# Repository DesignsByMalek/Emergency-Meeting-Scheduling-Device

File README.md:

# Integrated Documentation: Remote Emergency Meeting Scheduling Device

This comprehensive documentation merges two interconnected projects, combining IoT-enabled emergency scheduling with a Flask application to manage Google services. Together, they offer a robust solution for automating critical communication tasks.

---

## Project Overview

### License

This project is licensed under the Apache License 2.0. You may obtain a copy of the License at:

[Apache License 2.0](http://www.apache.org/licenses/LICENSE-2.0)

Unless required by applicable law or agreed to in writing, software distributed under the License is distributed on an "AS IS" BASIS, WITHOUT WARRANTIES OR CONDITIONS OF ANY KIND, either express or implied. See the License for the specific language governing permissions and limitations under the License.

---

### Remote Emergency Meeting Scheduling Device
An open-source IoT solution designed to automate emergency meeting scheduling. It integrates seamlessly with Google Meet, SMS triggers, and email notifications to enhance reliability and efficiency.

### Flask Application
A lightweight web application utilizing Google services to automate calendar and spreadsheet management, with SMS processing to trigger calendar invites.

---

## Features

### IoT Device Highlights
- **SMS Trigger**: Activates the backend server via Twilio to initiate emergency meeting scheduling.
- **Battery Efficiency**: Operates for over a year on a single battery.
- **Design Optimization**: Iteratively developed for enhanced functionality and aesthetics.
- **Complete Resources**: Includes PCB designs, 3D models, schematics, and manufacturing files.

### Backend Capabilities
- **Google Workspace Integration**: Automates Google Meet scheduling and retrieves client data from Google Sheets.
- **Email Notifications**: Sends meeting details to participants promptly.
- **Scalability**: Handles multiple requests in real-time.

### Flask App Features
- **Google Calendar Management**: Creates and customizes Google Calendar events, including attendees, timings, and reminders.
- **Spreadsheet Management**: Reads, writes, and appends data dynamically to Google Sheets.
- **SMS Processing**: Logs SMS data, retrieves client details, and triggers calendar invites based on the content.

---

## Installation

### Prerequisites
- **Software**: Python 3.8+
- **Google APIs**: Enable Calendar and Sheets APIs in the Google Cloud Console.
- **API Accounts**: Twilio account for SMS handling; OAuth credentials for Google services.

### Setup Steps

#### Clone the Repository
```bash
git clone <repository_url>
cd <repository_folder>
```

#### Install Dependencies
```bash
pip install -r requirements.txt
```

#### Configure API Credentials
- Save the credentials JSON file from Google Cloud in the project directory.
- Add API keys and credentials in `config.py`:
  ```python
  CREDENTIAL_FILE = 'path_to_credentials.json'
  CALENDAR_TOKEN = 'path_to_google_calendar_token.json'
  SHEET_TOKEN = 'path_to_google_sheet_token.json'
  GOOGLE_SHEET = 'spreadsheet_id'
  ```

#### Start the Server
```bash
python app.py
```

---

## Usage

### IoT Device
1. Activate the device to send an SMS trigger to the backend.
2. The backend:
   - Retrieves client details from Google Sheets.
   - Schedules a Google Meet session.
   - Sends email notifications to participants.

### Flask App

#### Calendar Management
- Use the `set_calendar` function to create events:
  ```python
  from modules.calendar_v1 import set_calendar

  invitees = ["example1@gmail.com", "example2@gmail.com"]
  set_calendar(invitees)
  ```

#### Google Sheets Management
- Perform operations with the `GoogleSheets` class:
  ```python
  from modules.sheets_v1 import GoogleSheets

  gs = GoogleSheets()
  # Read data
  data = gs.read_data("Sheet1", "A1:C10")
  print(data)
  # Write data
  values = [["Name", "Age"], ["Alice", 25], ["Bob", 30]]
  gs.write_data("Sheet1", "A1", values)
  # Append data
  new_rows = [["Charlie", 35]]
  gs.append_data("Sheet1", new_rows)
  ```

#### SMS Processing
- Endpoint for SMS:
  ```bash
  /emergency-button/inbound-emergency
  ```
- Example payload:
  ```json
  {
    "From": "+1234567890",
    "To": "+0987654321",
    "Body": "button_id,event_type,battery_health"
  }
  ```
- Functionality:
  - Logs SMS details to the `SMS Logs` sheet.
  - Retrieves client emails from the `Client Info` sheet.
  - Triggers calendar invites based on the SMS content.

---

## GoogleAuthenticator Class for Google API Authentication

### Description
The `GoogleAuthenticator` class is designed to streamline authentication with Google API services. It handles token management, credential verification, and API service building, making it easier to integrate with Google services like Calendar and Sheets.

### How It Works

#### Authentication Process
- Ensures tokens are valid or refreshes them if expired.
- Launches a local server to authenticate and save credentials if no token exists.
- Saves credentials for future use.

#### Service Building
- Builds a Google API service using authenticated credentials for interaction with APIs like Calendar and Sheets.

#### Example Use
- Authenticate and initialize Calendar API service:
  ```python
  from services.authenticator import GoogleAuthenticator

  auth = GoogleAuthenticator(service_name='calendar', version='v3')
  credentials = auth.get_authenticated(token_path='path/to/token.json', scope=['https://www.googleapis.com/auth/calendar'])
  calendar_service = auth.auth_build('calendar', 'v3', credentials)
  print("Calendar API initialized.")
  ```

---

## Python Code Structure

```
project_root/
    |- app/
    |   |- modules/
    |   |   |- calendar_v1.py   # Manages Google Calendar events
    |   |   |- sheets_v1.py     # Manages Google Sheets interactions
    |   |- services/
    |       |- authenticator.py # Google API authentication utility
    |   |- routes/
    |       |- sms.py           # Handles SMS processing and calendar integration
    |   |- config.py                 # Configuration file for environment variables
    |- app.py # Entry point
```
## Python Flow Chart 

---

## Future Improvements

- Enhance error handling for API operations.
- Add support for additional notification methods and triggers.
- Integrate further Google APIs for expanded functionality.
- PCB modifications for better user experience.

## IoT Device Code Highlights

### Key Functionalities
The Arduino code is designed to efficiently manage emergency meeting triggers. Below are the main highlights:

#### 1. **Low Power Mode**
The device leverages the `LowPower` library to maximize battery life by entering sleep mode when inactive.  
Example:
```cpp
#include "LowPower.h"

void sleepNow() {
    LowPower.powerDown(SLEEP_8S, ADC_OFF, BOD_OFF);  // Sleep for 8 seconds
}
```

#### 2. **Button Press Handling**
An interrupt is used to detect button presses and wake the device from sleep mode.
```cpp
const int buttonPin = 2;
volatile bool buttonPressed = false;

void setup() {
    attachInterrupt(digitalPinToInterrupt(buttonPin), wakeUp, FALLING);  // Attach interrupt
}

void wakeUp() {
    buttonPressed = true;  // Set flag on button press
}
```

#### 3. **SIM800L Communication**
The device uses `SoftwareSerial` to communicate with the SIM800L module for sending SMS triggers.
```cpp
#include <SoftwareSerial.h>

SoftwareSerial mySerial(3, 4);  // SIM800L Tx & Rx connected to pins 3 & 4

void sendSMS() {
    mySerial.begin(9600);
    mySerial.print("AT+CMGF=1
");  // Set SMS mode
    mySerial.print("AT+CMGS="+1234567890"
");  // Specify recipient
    mySerial.print("Emergency meeting triggered.
");  // Message content
    mySerial.write(26);  // End message with CTRL+Z
}
```
---

## Arduino Flow Chart

---

### Full Code
The complete code is available in the GitHub repository.

---

## Assembly Animation

---

## Done By

This project was created and maintained by:

- [GitDevKarim](https://github.com/GitDevKarim)
- [DesignsByMalek](https://github.com/DesignsByMalek)

Feel free to reach out to us for any questions or contributions!

<div style="display: flex; justify-content: center; align-items: center;">
  <div style="text-align: center; margin-right: 20px;">
    <h3>GitDevKarim</h3>
    <span style="display: inline-block; margin-right: 10px;">
      
    </span>
    <span style="display: inline-block;">
      
    </span>
  </div>

  <div style="height: 50px; width: 1px; background-color: #000;"></div>

  <div style="text-align: center; margin-left: 20px;">
    <h3>DesignsByMalek</h3>
    <span style="display: inline-block; margin-right: 10px;">
      
    </span>
    <span style="display: inline-block;">
      
    </span>
  </div>
</div>

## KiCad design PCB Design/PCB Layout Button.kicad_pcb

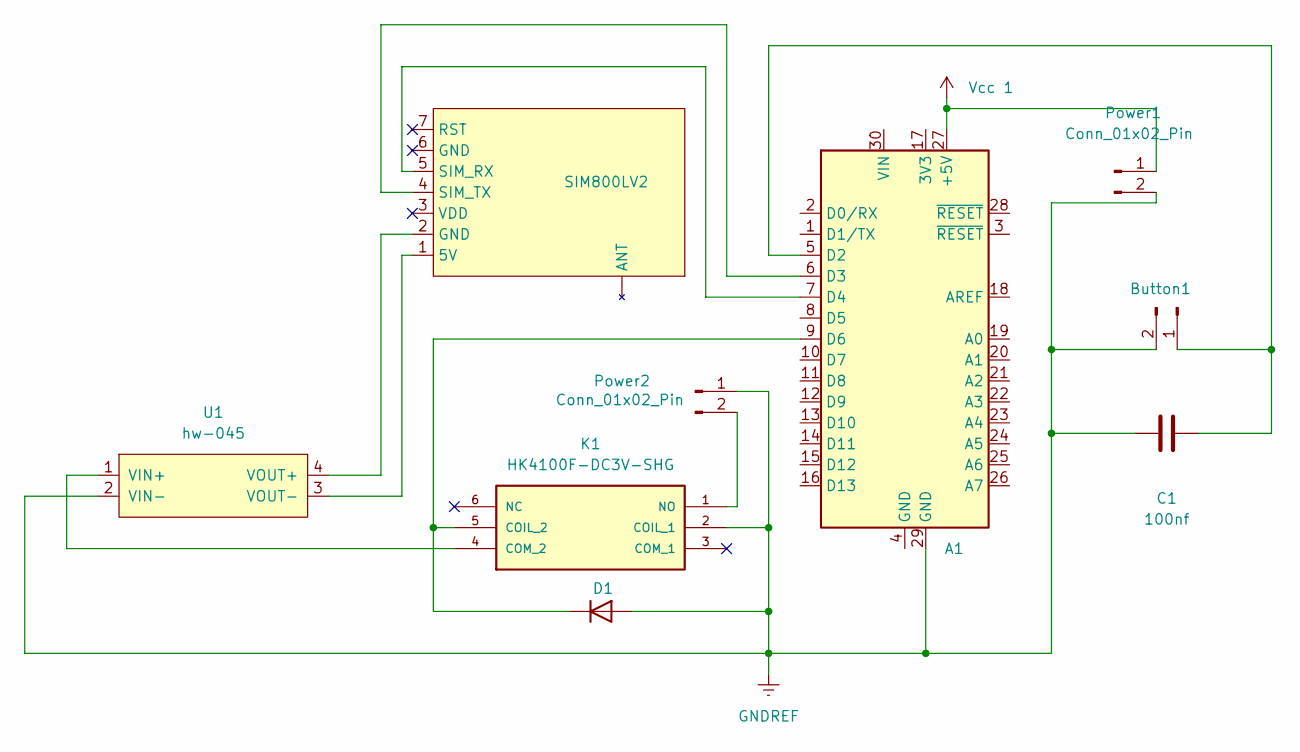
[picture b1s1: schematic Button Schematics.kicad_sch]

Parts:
A1: Arduino_Nano_v3.x; Arduino_Nano
Button1: Conn_01x02_Pin; JST_EH_B2B-EH-A_1x02_P2.50mm_Vertical
C1: 100nf; C_Disc_D5.1mm_W3.2mm_P5.00mm
D1: D; D_DO-35_SOD27_P7.62mm_Horizontal
K1: HK4100F-DC3V-SHG; HK4100FDC5VSHG; MANUFACTURER_PART_NUMBER HK4100F-DC5V-SHG
Power1, Power2: Conn_01x02_Pin; JST_EH_B2B-EH-A_1x02_P2.50mm_Vertical
SIM800LV2: SIM800
U1: hw-045; MT3608_module

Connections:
GNDREF: A1.29 (GND), Button1.2, C1.1, D1.2 (A), K1.2 (COIL_1), Power1.2, Power2.1, U1.2 (VIN-)
unnamed: A1.5 (D2), Button1.1, C1.2
unnamed: A1.6 (D3), SIM800LV2.4 (SIM_TX)
unnamed: A1.7 (D4), SIM800LV2.5 (SIM_RX)
unnamed: A1.9 (D6), D1.1 (K), K1.5 (COIL_2)
unnamed: K1.4 (COM_2), U1.1 (VIN+)
unnamed: K1.1 (NO), Power2.2
unnamed: SIM800LV2.1 (5V), U1.3 (VOUT-)
unnamed: SIM800LV2.2 (GND), U1.4 (VOUT+)
Vcc 1: A1.27 (+5V), Power1.1

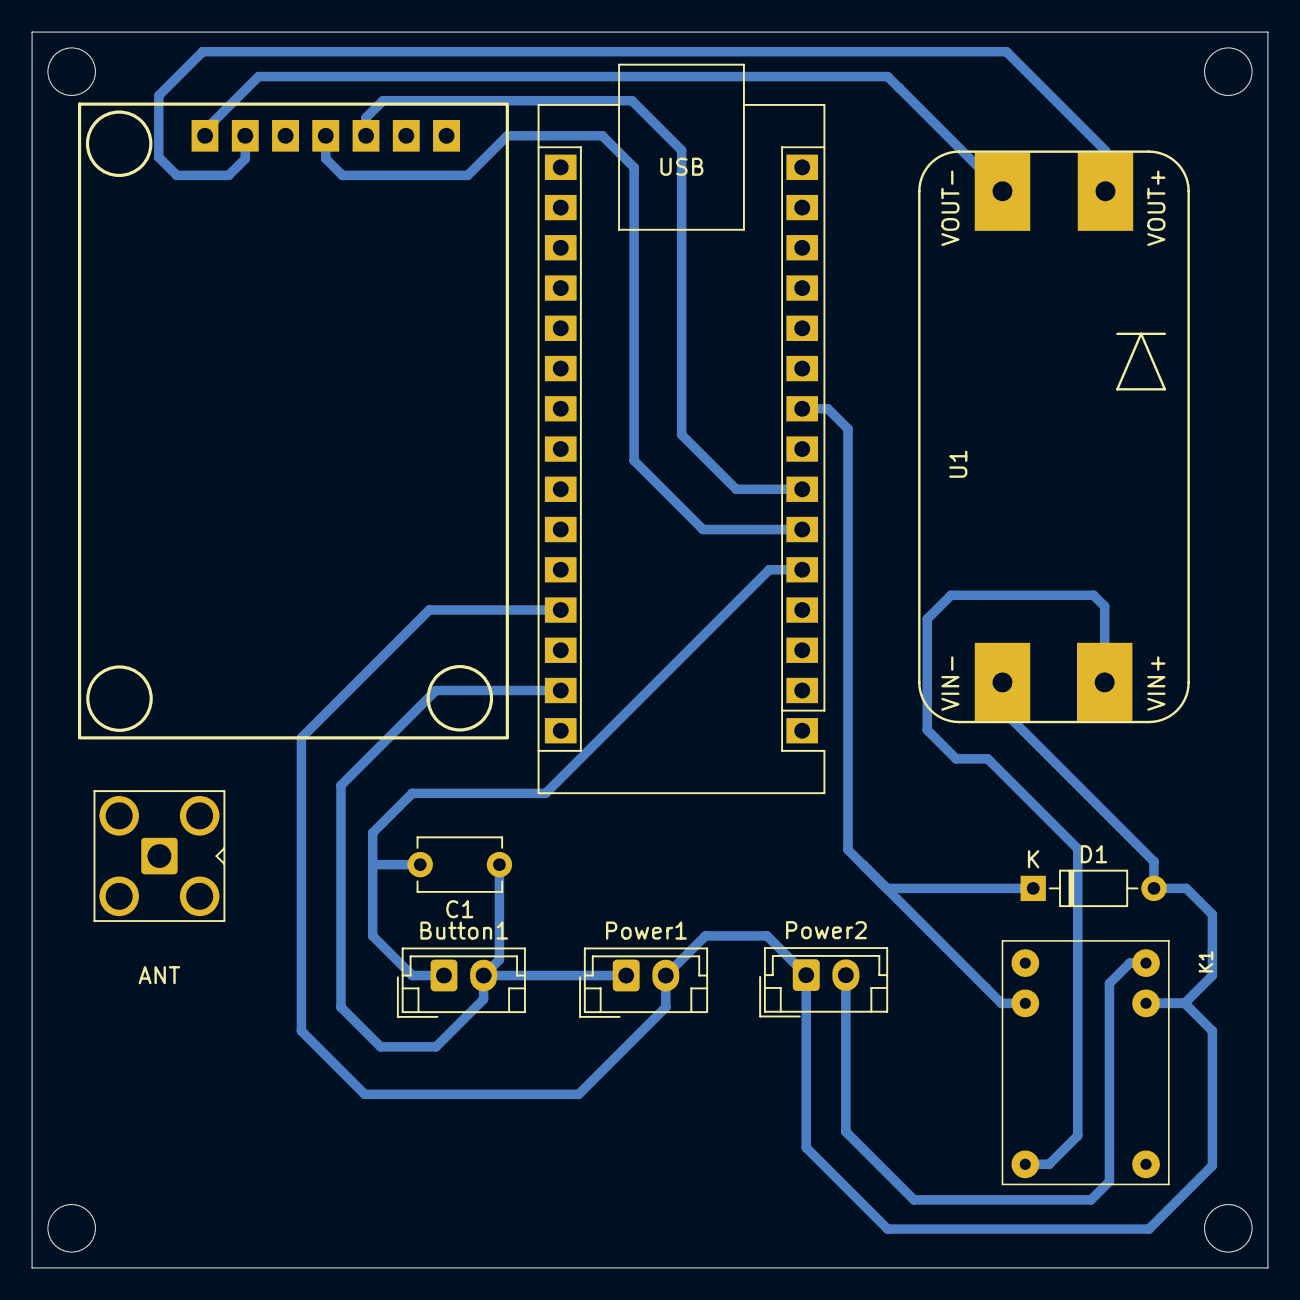
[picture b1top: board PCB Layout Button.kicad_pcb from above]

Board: 2 copper layers, 78.0 x 78.0 mm, 10 parts (0 on the bottom side), 10 nets.

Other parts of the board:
ANT: SMA_Amphenol_901-143_Horizontal

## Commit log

2025-01-03 README.md
2025-01-03 Sim800L_Test.ino
2025-01-03 Flask App
2025-01-04 Flow chart
2025-01-04 Assests
